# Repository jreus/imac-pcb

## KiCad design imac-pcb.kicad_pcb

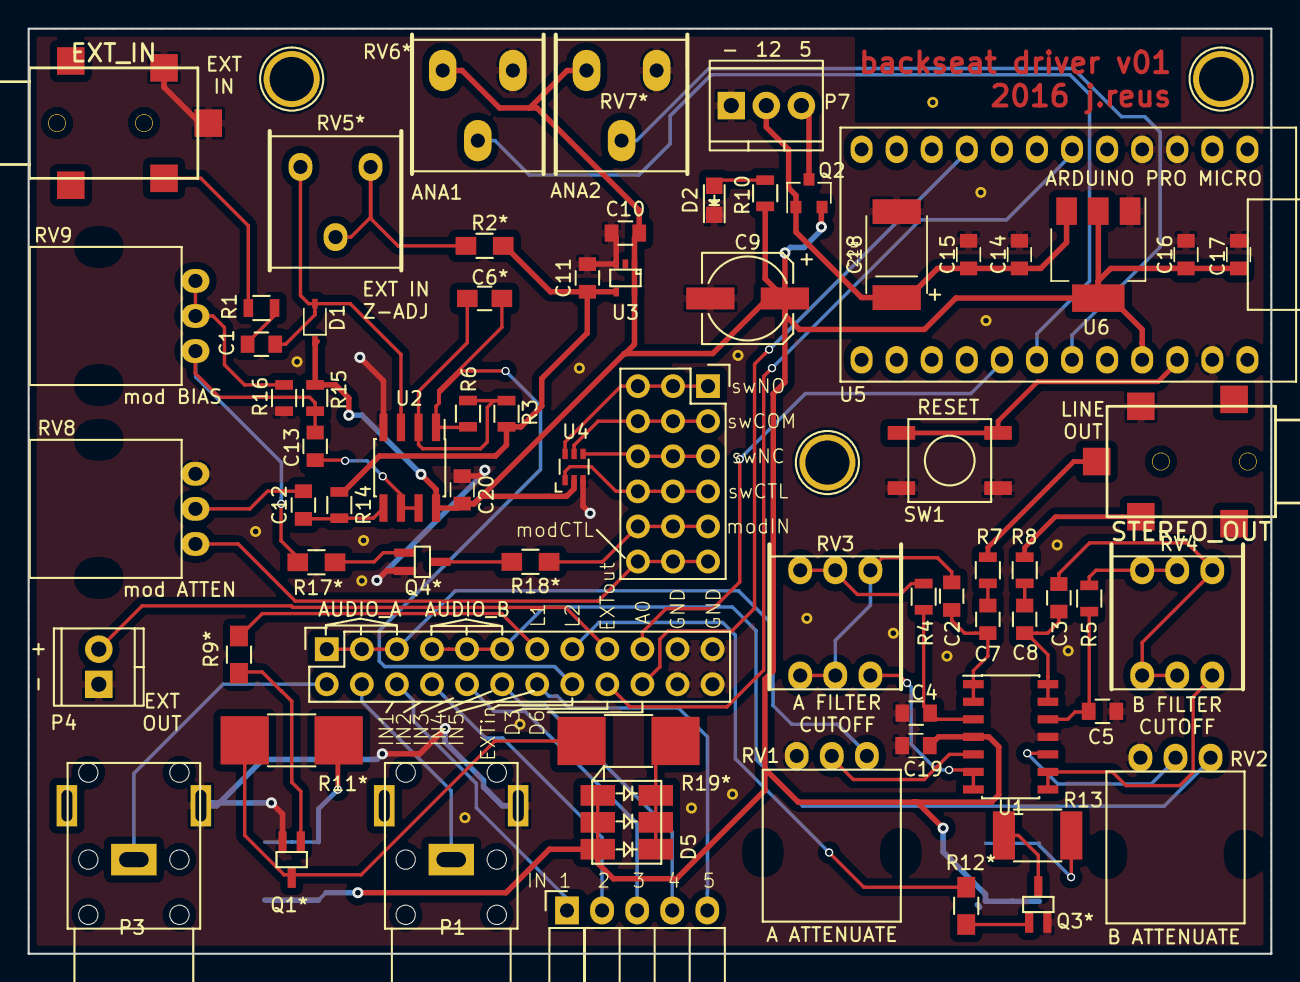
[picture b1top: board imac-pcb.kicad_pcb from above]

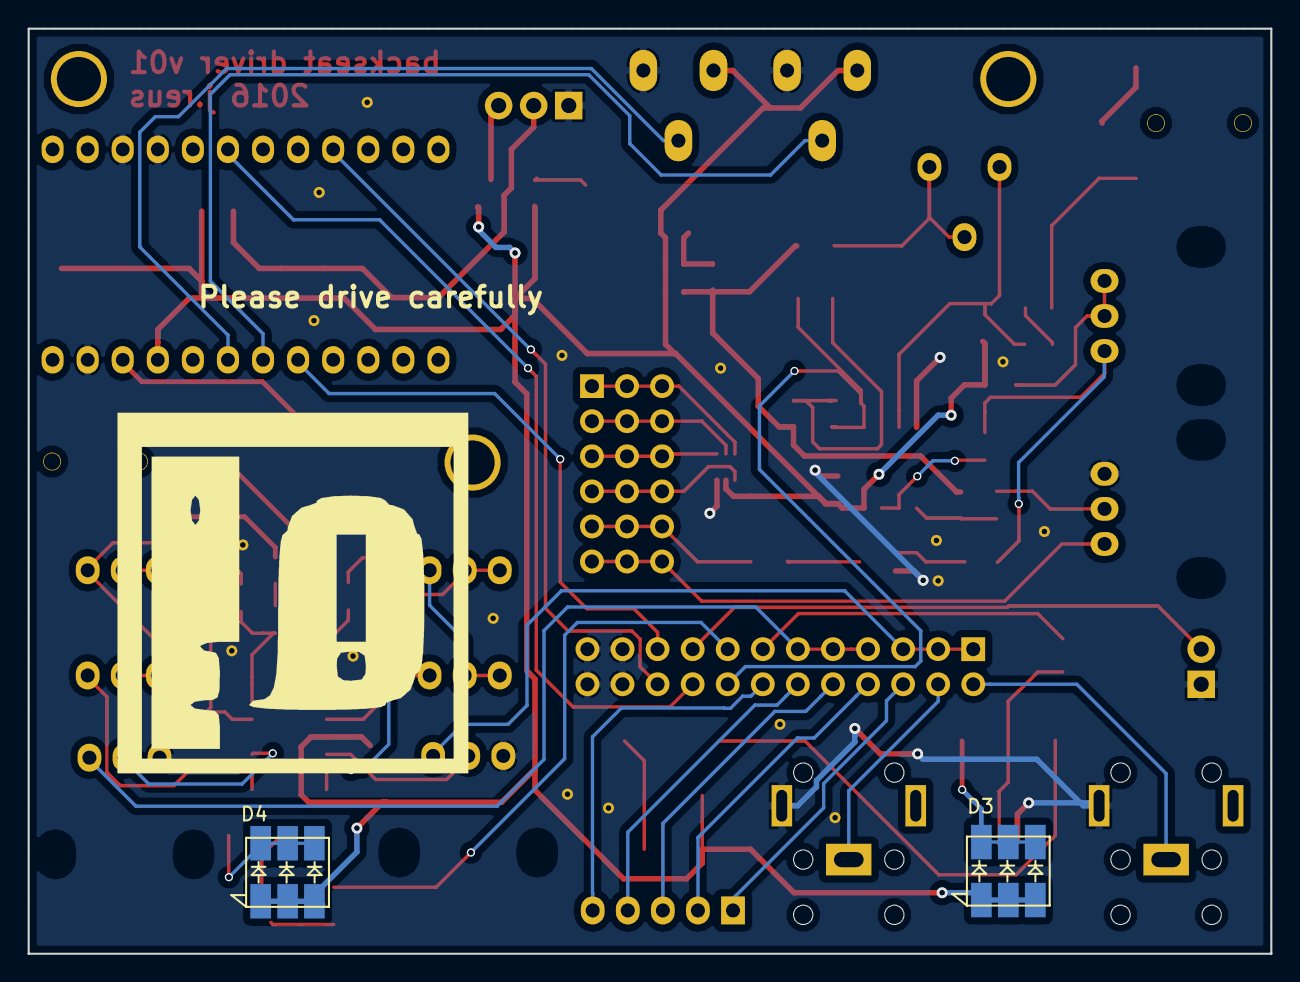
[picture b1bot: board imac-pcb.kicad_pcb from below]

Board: 2 copper layers, 90.0 x 67.0 mm, 73 parts (2 on the bottom side), 66 nets.

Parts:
C1, C7, C8, C10, C11, C12, C13, C14, C17: 1u; C_0805
C2, C3: 68n; C_0805
C4, C5: 10n; C_0805
C6*: 220p*; C_0805_HandSoldering
C9: 220u; c_elec_6.3x7.7
C15, C16, C19, C20: 100n; C_0805
C18: 22u; 2917C
D1: 1N4148; SOD-323F
D2: KP-2012LSGC; LED_0805
D3, D4, D5: CLP6B-WKW; PLCC6-3in1-SMD-LED
J1: EXT_IN; Lumberg_1503_03
J2: STEREO_OUT; Lumberg_1503_03
P1: PROBE1; PSG01546_RCA_Phono_Connector
P2: PATCHBAY_IO; Socket_Strip_Straight_2x12
P3: PROBE2; PSG01546_RCA_Phono_Connector
P4: EXT_OUT; TerminalBlock_TE_282834-2-2.54mm_2pol
P5: INPUTS; Socket_Strip_Angled_1x05
P6: PATCHBAY_A; Socket_Strip_Straight_3x06
P7: PWR_X3; TerminalBlock_TE_282834-3-2.54mm_3pol
Q1*, Q3*, Q4*: NX3008N***; SC-70-BIG-PADS
Q2: PMV48XP; SOT-23
R1: 33k; R_0805
R2*: 100**; R_0805_HandSoldering
R3: 1k; R_0805
R4, R5: 220; R_0805
R6, R15: 3k3; R_0805
R7, R8, R16: 100; R_0805
R9*, R12*, R17*: 100***; R_0805_HandSoldering
R10: 1k5; R_0805
R11*, R19*: 27****; R_1812_HandSoldering
R13: 27; R_1812
R14: 1meg; R_0805
R18*: 100*; R_0805_HandSoldering
RV1, RV2, RV8, RV9: 100k; Pot_Bourns_PTV09A-4_Horizontal_Rear_mount
RV3, RV4: 100k; Dual_Pot_Bourns_3301H-00X
RV5*: 100k**; Trimpot_Bourns_3386F_Vishay_M63
RV6*, RV7*: 100k†; Trimpot_Bourns_Big_Pads_3386F_Vishay_M63
SW1: RESET_SW; EVQ_BUT
U1: MCP6004; SOIC-14_3.9x8.7mm_Pitch1.27mm
U2: MCP6002; SOIC-8_3.9x4.9mm_Pitch1.27mm_handsolder
U3: NCP4620; SC-70-5
U4: ADG849; SC-70-6
U5: arduino_pro_micro
U6: NCP1117-5; SOT-223

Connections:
2V5_REF: C11.1, R2*.2, R3.2, R14.2, U3.4
5V_IN: P7.3, Q2.3
5V_SYS: C9.1, C10.1, C16.1, C17.1, C19.1, C20.1, D1.1, D3.1, D3.2, D3.3, D4.1, D4.2, D4.3, D5.1, D5.2, D5.3, Q2.2, R10.1, R15.1, RV6*.1, RV7*.1, U1.4, U2.8, U3.1, U3.5, U4.2, U5.21, U6.2, U6.4
12V_IN: C14.1, C15.1, C18.1, P7.2, Q2.1, U6.3
/A0_IN: P2.19, U5.17
/A1_IN: RV6*.2, U5.18
/A2_IN: RV7*.2, U5.19
/AUDIOA_SEND: P2.1, P2.3, P2.5, RV1.1
/AUDIOB_SEND: P2.7, P2.9, P2.11, RV2.1
/D3: P2.18, U5.6
/D6: P2.20, U5.9
/EXT_IN: C6*.1, P2.16, R6.1, U2.1
/EXT_OUT: P2.17, P4.2
/IN1: P2.6, P5.1
/IN2: P2.8, P5.2
/IN3: P2.10, P5.3
/IN4: P2.12, P5.4
/IN5: P2.14, P5.5
/LED_CTRL1: P2.13, R9*.2
/LED_CTRL2: P2.15, R12*.2
/MOD_CTRL: P6.16, P6.17, P6.18, RV8.1
/MOD_OUT: P6.13, P6.14, P6.15, R18*.1
/PB1: P2.2, P3.1
/PB2: P1.1, P2.4
/SWA_COM: P6.4, P6.5, P6.6, U4.5
/SWA_CTRL: P6.10, P6.11, P6.12, U4.1
/SWA_NC: P6.7, P6.8, P6.9, U4.4
/SWA_NO: P6.1, P6.2, P6.3, U4.6
GND: C4.2, C5.2, C9.2, C10.2, C11.2, C14.2, C15.2, C16.2, C17.2, C18.2, C19.2, C20.2, D2.1, J1.2, J1.3, J2.1, P1.2, P2.21, P2.22, P2.23, P2.24, P3.2, P4.1, P7.1, Q1*.2, Q3*.2, Q4*.2, R16.2, RV1.3, RV2.3, RV6*.3, RV7*.3, RV8.3, SW1.1, U1.11, U2.4, U3.3, U4.3, U5.3, U5.4, U5.23, U6.1
unnamed: C1.1, D1.2, RV5*.1, U2.3
unnamed: C1.2, R1.1
unnamed: C2.1, C7.2, U1.1, U1.2
unnamed: C2.2, RV3.2, RV3.3, RV3.4
unnamed: C3.1, C8.2, U1.13, U1.14
unnamed: C3.2, RV4.2, RV4.3, RV4.4
unnamed: C4.1, R4.1, U1.3
unnamed: C5.1, R5.1, U1.12
unnamed: C6*.2, R3.1, R6.2, U2.2
unnamed: C7.1, R7.2
unnamed: C8.1, R8.2
unnamed: C12.1, R14.1, U2.5
unnamed: C12.2, RV8.2
unnamed: C13.1, R15.2, R17*.2, RV9.1
unnamed: C13.2, U2.6, U2.7
unnamed: D2.2, R10.2
unnamed: D3.4, D3.5, D3.6, R11*.1
unnamed: D4.4, D4.5, D4.6, R13.1
unnamed: D5.4, D5.5, D5.6, R19*.1
unnamed: J1.1, R1.2
unnamed: J2.2, R7.1
unnamed: J2.3, R8.1
unnamed: Q1*.1, R9*.1
unnamed: Q1*.3, R11*.2, R19*.2
unnamed: Q3*.1, R12*.1
unnamed: Q3*.3, R13.2
unnamed: Q4*.1, R17*.1
unnamed: Q4*.3, R18*.2
unnamed: R2*.1, RV5*.2, RV5*.3
unnamed: R4.2, RV3.5, RV3.6
unnamed: R5.2, RV4.5, RV4.6
unnamed: R16.1, RV9.2, RV9.3
unnamed: RV1.2, U1.5
unnamed: RV2.2, U1.10
unnamed: RV3.1, U1.6, U1.7
unnamed: RV4.1, U1.8, U1.9
unnamed: SW1.2, U5.22

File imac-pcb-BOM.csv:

Reference, Value, Footprint, Datasheet,In Hand?
C1,1u,Capacitors_SMD:C_0805,,x
C10,1u,Capacitors_SMD:C_0805,,x
C11,1u,Capacitors_SMD:C_0805,,x
C12,1u,Capacitors_SMD:C_0805,,x
C13,1u,Capacitors_SMD:C_0805,,x
C14,1u,Capacitors_SMD:C_0805,,x
C15,100n,Capacitors_SMD:C_0805,,x
C16,100n,Capacitors_SMD:C_0805,,x
C17,1u,Capacitors_SMD:C_0805,,x
C18,22u,Imac:2917C,,
C19,100n,Capacitors_SMD:C_0805,,x
C2,68n,Capacitors_SMD:C_0805,,x
C20,100n,Capacitors_SMD:C_0805,,x
C3,68n,Capacitors_SMD:C_0805,,x
C4,10n,Capacitors_SMD:C_0805,,x
C5,10n,Capacitors_SMD:C_0805,,x
C6,220p*,Capacitors_SMD:C_0805_HandSoldering,,x
C7,1u,Capacitors_SMD:C_0805,,x
C8,1u,Capacitors_SMD:C_0805,,x
C9,220u,Capacitors_SMD:c_elec_6.3x7.7,,
D1,1N4148,Imac:SOD-323F,,
D2,KP-2012LSGC,LEDs:LED_0805,,
D3,CLP6B-WKW,Imac:PLCC6-3in1-SMD-LED,,
D4,CLP6B-WKW,Imac:PLCC6-3in1-SMD-LED,,
D5,CLP6B-WKW,Imac:PLCC6-3in1-SMD-LED,,
J1,EXT_IN,Lumberg:Lumberg_1503_03,,x
J2,STEREO_OUT,Lumberg:Lumberg_1503_03,,x
P1,PROBE1,Imac:PSG01546_RCA_Phono_Connector,,x
P2,PATCHBAY_IO,Socket_Strips:Socket_Strip_Straight_2x12,,
P3,PROBE2,Imac:PSG01546_RCA_Phono_Connector,,x
P4,EXT_OUT,Imac:TerminalBlock_TE_282834-2-2.54mm_2pol,,x
P5,INPUTS,Socket_Strips:Socket_Strip_Angled_1x05,,
P6,PATCHBAY_A,Imac:Socket_Strip_Straight_3x06,,
P7,PWR_X3,Imac:TerminalBlock_TE_282834-3-2.54mm_3pol,,x
Q1,NX3008N***,imac:SC-70-BIG-PADS,,
Q2,PMV48XP,TO_SOT_Packages_SMD:SOT-23,,
Q3,NX3008N***,imac:SC-70-BIG-PADS,,
Q4,NX3008N***,imac:SC-70-BIG-PADS,,
R1,33k,Resistors_SMD:R_0805,,
R10,1k5,Resistors_SMD:R_0805,,
R11,27****,Resistors_SMD:R_1812_HandSoldering,,
R12,100***,Resistors_SMD:R_0805_HandSoldering,,
R13,27,Resistors_SMD:R_1812,,
R14,1meg,Resistors_SMD:R_0805,,
R15,3k3,Resistors_SMD:R_0805,,
R16,100,Resistors_SMD:R_0805,,
R17,100***,Resistors_SMD:R_0805_HandSoldering,,
R18,100*,Resistors_SMD:R_0805_HandSoldering,,
R19,27****,Resistors_SMD:R_1812_HandSoldering,,
R2,100**,Resistors_SMD:R_0805_HandSoldering,,
R3,1k,Resistors_SMD:R_0805,,
R4,220,Resistors_SMD:R_0805,,
R5,220,Resistors_SMD:R_0805,,
R6,3k3,Resistors_SMD:R_0805,,
R7,100,Resistors_SMD:R_0805,,
R8,100,Resistors_SMD:R_0805,,
R9,100***,Resistors_SMD:R_0805_HandSoldering,,
RV1,100k,Imac:Pot_Bourns_PTV09A-4_Horizontal_Rear_mount,,x
RV2,100k,Imac:Pot_Bourns_PTV09A-4_Horizontal_Rear_mount,,x
RV3,100k,Imac:Dual_Pot_Bourns_3301H-00X,,
RV4,100k,Imac:Dual_Pot_Bourns_3301H-00X,,
RV5,100k**,Imac:Trimpot_Bourns_3386F_Vishay_M63,,
RV6,100k†,Imac:Trimpot_Bourns_Big_Pads_3386F_Vishay_M63,,
RV7,100k†,Imac:Trimpot_Bourns_Big_Pads_3386F_Vishay_M63,,
RV8,100k,Imac:Pot_Bourns_PTV09A-4_Horizontal_Rear_mount,,x
RV9,100k,Imac:Pot_Bourns_PTV09A-4_Horizontal_Rear_mount,,x
SW1,RESET_SW,Imac:EVQ_BUT,,
U1,MCP6004,Housings_SOIC:SOIC-14_3.9x8.7mm_Pitch1.27mm,,
U2,MCP6002,Imac:SOIC-8_3.9x4.9mm_Pitch1.27mm_handsolder,,
U3,NCP4620,TO_SOT_Packages_SMD:SC-70-5,,
U4,ADG849,TO_SOT_Packages_SMD:SC-70-6,,
U5,arduino_pro_micro,Imac:arduino_pro_micro,,
U6,NCP1117-5,TO_SOT_Packages_SMD:SOT-223,,

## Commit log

2016-12-22 git ignore file
2016-12-22 documentation folder with datasheets
2016-12-22 initial project commit
2016-12-27 updated documentation
2016-12-27 added BOM
2016-12-27 schematic changes & moved datasheet files
2016-12-27 updated top-level flowchart and fixed issues with simulations
2016-12-27 updated bom
2016-12-27 small schematic updates
2016-12-30 some bugs repaired in simulations
2016-12-30 new datasheets
2016-12-30 updated system flowchart
2016-12-30 continued work on schematics
2017-01-03 new component datasheets
2017-01-03 simulations for CREE SMD leds and driver circuits
2017-01-03 bom updates
2017-01-03 updated datasheets
2017-01-03 simulation of p-fet voltage chooser
2017-01-03 added schematic libs for cree and nx semiconductor components
2017-01-03 added led drivers, voltage selector, power conditioning to the schematic
2017-01-06 modifications to schematic libraries
2017-01-06 new footprint modules for PLCC6 and SOD-323F
2017-01-06 added datasheets for power led and trimpots
2017-01-06 begin work on pcb layout
2017-01-07 added additional datasheets for pots and terminal blocks
2017-01-07 created footprint modules for Arduino micro, trimpots, RCA plug, patchbays, terminal blocks
2017-01-07 added printable schematic
2017-01-07 small updates to schematic symbols
2017-01-07 updates to BOM
2017-01-07 begin layout of pcb
2017-01-16 updated print schematic
2017-01-16 new footprints added
2017-01-16 added new schematic symbols
2017-01-16 major work on PCB layout
2017-01-19 added via modules
2017-01-19 modified SC70 and PLCC6 modules
2017-01-19 finished routing & moving references in silkscreen
2017-01-19 first draft of gerbers
2017-01-19 front and back 3d pngs
2017-01-29 added datasheets and printable schematic and pcb
2017-01-29 susan kare and other graphic components
2017-01-29 final gerbers for v01 run
2017-01-29 final schematic for run v01
